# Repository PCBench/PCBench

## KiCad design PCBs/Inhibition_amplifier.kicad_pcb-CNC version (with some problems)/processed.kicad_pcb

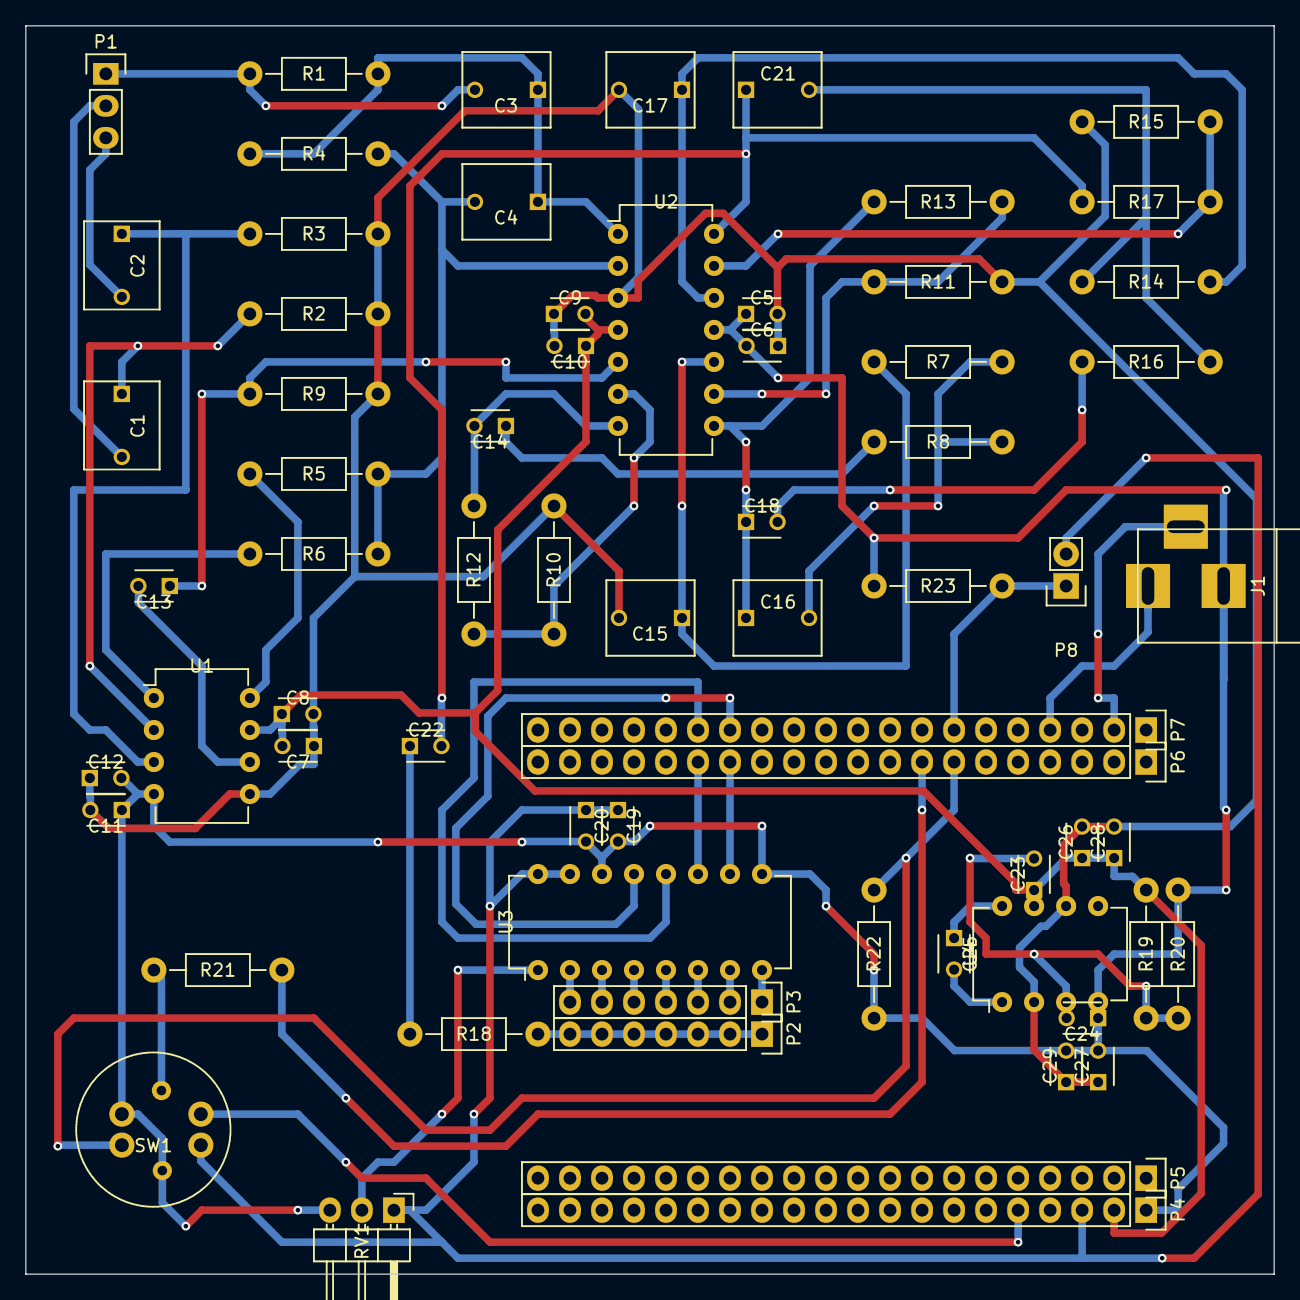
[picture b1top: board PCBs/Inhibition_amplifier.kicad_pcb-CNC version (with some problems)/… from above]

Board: 2 copper layers, 99.1 x 99.1 mm, 67 parts (0 on the bottom side), 51 nets.

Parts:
C1, C2: 0.01μ; C_Rect_L7_W6_P5
C3, C4: 1n; C_Rect_L7_W6_P5
C5, C7, C9, C11, C19: 0.01μ; C_Disc_D3_P2.5
C6, C8, C10, C12, C20: 0.33μ; C_Disc_D3_P2.5
C13, C14, C18, C22, C28, C29: 10μ; C_Disc_D3_P2.5
C15, C17: 0.47μ; C_Rect_L7_W6_P5
C16, C21: 0.82μ; C_Rect_L7_W6_P5
C23, C24: .01μ; C_Disc_D3_P2.5
C25: 1n; C_Disc_D3_P2.5
C26, C27: 1μ; C_Disc_D3_P2.5
J1: JACK_2P; BARREL_JACK
P1: CONN_01X03; Pin_Header_Straight_1x03
P2, P3: CONN_01X07; Pin_Header_Straight_1x07
P4, P5, P6, P7: CONN_01X20; Pin_Header_Straight_1x20
P8: CONN_01X02; Pin_Header_Straight_1x02
R1, R4: 100K; Resistor_Horizontal_RM10mm
R2, R3: 15M; Resistor_Horizontal_RM10mm
R5, R6: 100; Resistor_Horizontal_RM10mm
R7, R8, R9, R10, R11, R14, R15, R16, R19, R22, R23: 10K; Resistor_Horizontal_RM10mm
R12, R13, R17: 470K; Resistor_Horizontal_RM10mm
R18: 220; Resistor_Horizontal_RM10mm
R20: 15K; Resistor_Horizontal_RM10mm
R21: 1K; Resistor_Horizontal_RM10mm
RV1: POT; Pin_Header_Angled_1x03
SW1: Switch_DPST; Switch_LED
U1: AD620; DIP-8_W7.62mm
U2: LM324; DIP-14_W7.62mm
U3: MCP3008; DIP-16_W7.62mm
U4: CA3140; DIP-8_W7.62mm

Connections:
GND: C5.2, C6.1, C7.1, C8.2, C9.1, C10.2, C11.2, C12.1, C15.2, C17.2, C26.2, C27.1, C28.2, C29.1, R2.2, R3.2, R9.2, R10.2, R11.2, R15.2, U1.5, U2.3, U4.2, U4.6
unnamed: C1.1, R2.1, U1.2
unnamed: C1.2, P1.2
unnamed: C2.1, R3.1, U1.3
unnamed: C2.2, P1.3
unnamed: C3.1, C4.1, R1.1, R4.1, U2.1
unnamed: C3.2, P1.1, R1.2
unnamed: C4.2, R4.2, R5.2, R6.1, U2.2
unnamed: C13.1, R9.1, U2.5
unnamed: C13.2, U1.6
unnamed: C14.1, R8.2
unnamed: C14.2, R12.1, U2.7
unnamed: C15.1, R7.1, U2.10
unnamed: C16.1, C18.1, R13.1, U2.8
unnamed: C16.2, R7.2, R8.1
unnamed: C17.1, R14.2, U2.12
unnamed: C18.2, R16.2
unnamed: C19.1, C20.1, P4.3, P8.2, RV1.1, SW1.4, U3.15, U3.16
unnamed: C21.1, C22.2, R17.1, U2.14
unnamed: C21.2, R14.1, R16.1
unnamed: C22.1, R18.1
unnamed: C23.2, C24.2, R19.2, R20.1, U4.3
unnamed: C25.1, U4.8
unnamed: C25.2, U4.1
unnamed: J1.1, P7.4
unnamed: J1.3, P7.2
unnamed: P2.1, P2.2, P2.3, P2.4, P2.5, P2.6, P2.7, R18.2
unnamed: P3.1, U3.8
unnamed: P3.2, U3.7
unnamed: P3.3, U3.6
unnamed: P3.4, U3.5
unnamed: P3.5, U3.4
unnamed: P3.6, U3.3
unnamed: P3.7, U3.2
unnamed: P4.5, SW1.2
unnamed: P6.7, R22.1, SW1.3
unnamed: P6.8, R21.2
unnamed: P6.14, U3.10
unnamed: P6.15, U3.11
unnamed: P7.7, P8.1, R23.1
unnamed: P7.14, U3.13
unnamed: P7.15, U3.12
unnamed: R5.1, U1.8
unnamed: R6.2, U1.1
unnamed: R10.1, R12.2, U2.6
unnamed: R11.1, R13.2, U2.9
unnamed: R15.1, R17.2, U2.13
unnamed: R21.1, SW1.5
unnamed: RV1.2, U3.1
VCC: C7.2, C8.1, C9.2, C10.1, C23.1, C26.1, C28.1, P4.2, R19.1, U1.7, U2.4, U4.7
VEE: C5.1, C6.2, C11.1, C12.2, C19.2, C20.2, C24.1, C27.2, C29.2, J1.2, P4.1, R20.2, R22.2, R23.2, RV1.3, SW1.1, SW1.6, U1.4, U2.11, U3.9, U3.14, U4.4

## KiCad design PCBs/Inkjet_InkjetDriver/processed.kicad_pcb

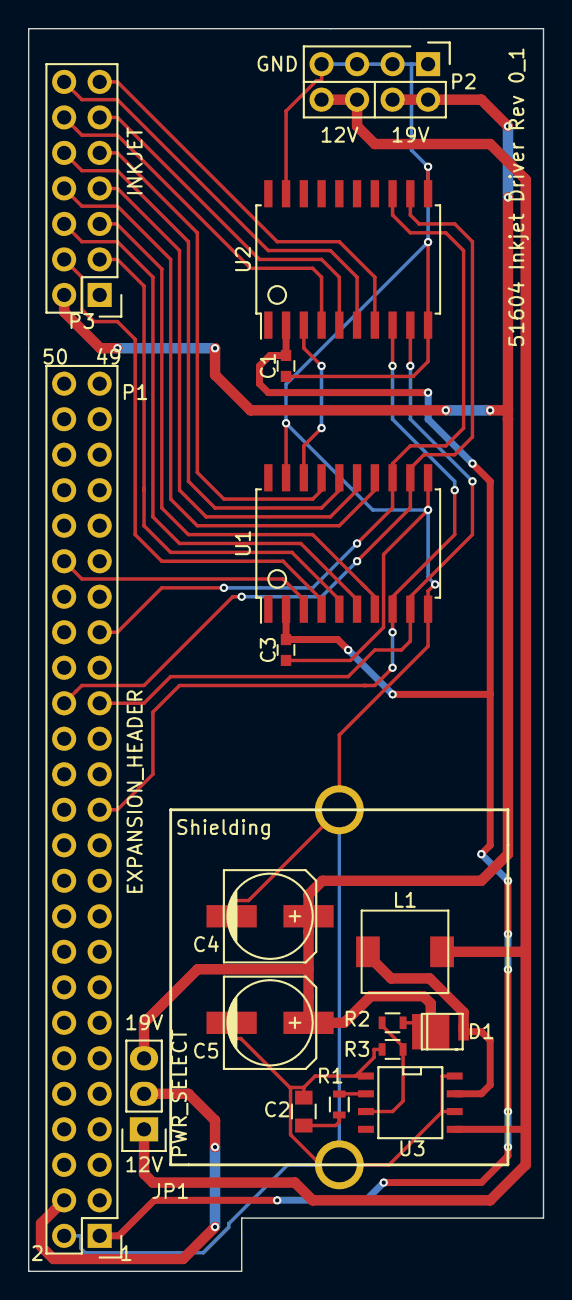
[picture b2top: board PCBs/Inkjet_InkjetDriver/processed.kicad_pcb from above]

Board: 2 copper layers, 36.8 x 88.9 mm, 19 parts (0 on the bottom side), 27 nets.

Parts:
C1, C3: 0.1uF; C_0603
C2: 1uF; C_0805
C4, C5: 100uF; c_elec_6.3x7.7
D1: SS3P4; DO-220_Diode
JP1: PWR_SELECT; Socket_Strip_Straight_1x03
L1: 220uH; CLF6045_Inductor
P1: EXPANSION_HEADER; Pin_Header_Straight_2x25
P2: PWR; Pin_Header_Straight_2x04_Silk_Change
P3: INKJET; Pin_Header_Straight_2x07
R1: 1k; R_0603
R2: 18.7k; R_0603
R3: 1.27k; R_0603
SM1: Shielding; SolderWirePad_single_2-5mmDrill
SM2: Shield; SolderWirePad_single_2-5mmDrill
U1, U2: 6B595; SOIC-20_7.5x12.8mm_Pitch1.27mm
U3: LT1072; SOIC-8-N

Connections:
19V: C4.1, C5.1, D1.1, JP1.3, P2.2, P2.4, P3.2, R2.1
+5V: C1.1, C3.1, P1.1, U1.2, U2.2
+12V: JP1.1, L1.1, P2.6, P2.8, U3.5
GND: C1.2, C2.2, C3.2, C4.2, C5.2, P1.2, P2.1, P2.3, P2.5, P2.7, R3.2, SM1.1, SM2.1, U1.10, U1.11, U1.19, U2.10, U2.11, U2.19, U3.1, U3.6, U3.8
unnamed: C2.1, R1.2
unnamed: D1.2, L1.2, U3.7
unnamed: JP1.2, P1.4
unnamed: P1.25, U1.8, U2.8
unnamed: P1.31, U1.9, U2.9
unnamed: P1.32, U1.12, U2.12
unnamed: P1.35, U1.13, U2.13
unnamed: P1.40, U1.3
unnamed: P3.3, U1.5
unnamed: P3.4, U1.4
unnamed: P3.5, U1.7
unnamed: P3.6, U1.6
unnamed: P3.7, U1.15
unnamed: P3.8, U1.14
unnamed: P3.9, U1.17
unnamed: P3.10, U1.16
unnamed: P3.11, U2.5
unnamed: P3.12, U2.4
unnamed: P3.13, U2.7
unnamed: P3.14, U2.6
unnamed: R1.1, U3.2
unnamed: R2.2, R3.1, U3.3
unnamed: U1.18, U2.3

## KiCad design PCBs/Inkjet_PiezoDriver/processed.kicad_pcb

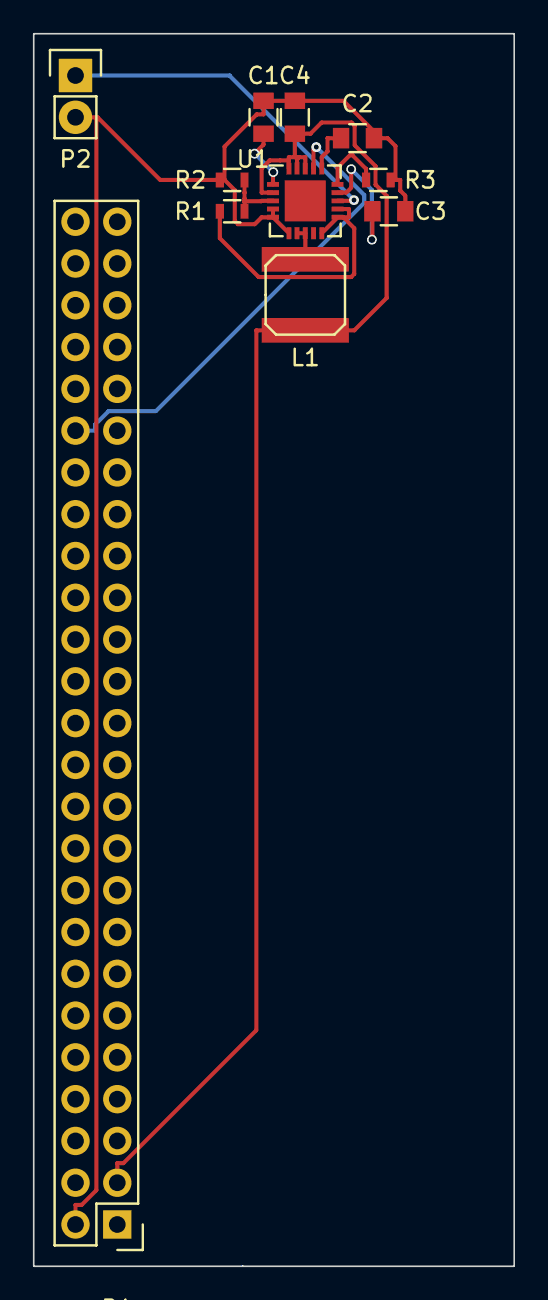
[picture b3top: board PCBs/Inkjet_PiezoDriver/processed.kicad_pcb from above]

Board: 2 copper layers, 29.2 x 74.9 mm, 11 parts (0 on the bottom side), 11 nets.

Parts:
C1, C2, C3, C4: C; C_0805
L1: INDUCTOR; SELF-WE-TPC_M
P1: CONN_02X25; Pin_Header_Straight_2x25
P2: CONN_01X02; Pin_Header_Straight_1x02
R1, R2, R3: R; R_0603
U1: DRV8662; QFN-20-1EP_4x4mm_Pitch0.5mm

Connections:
GND: C1.2, C2.2, C3.2, C4.2, P1.2, P2.2, R2.2, R3.1, U1.4, U1.5, U1.6
unnamed: C1.1, U1.1
unnamed: C2.1, U1.16
unnamed: C3.1, U1.14
unnamed: L1.2, U1.7, U1.8
unnamed: P1.40, U1.17
unnamed: P2.1, U1.13
unnamed: R1.1, U1.10, U1.11, U1.12
unnamed: R1.2, R2.1, U1.3
unnamed: R3.2, U1.15
VDD: C4.1, L1.1, P1.3, U1.2, U1.18, U1.19, U1.20

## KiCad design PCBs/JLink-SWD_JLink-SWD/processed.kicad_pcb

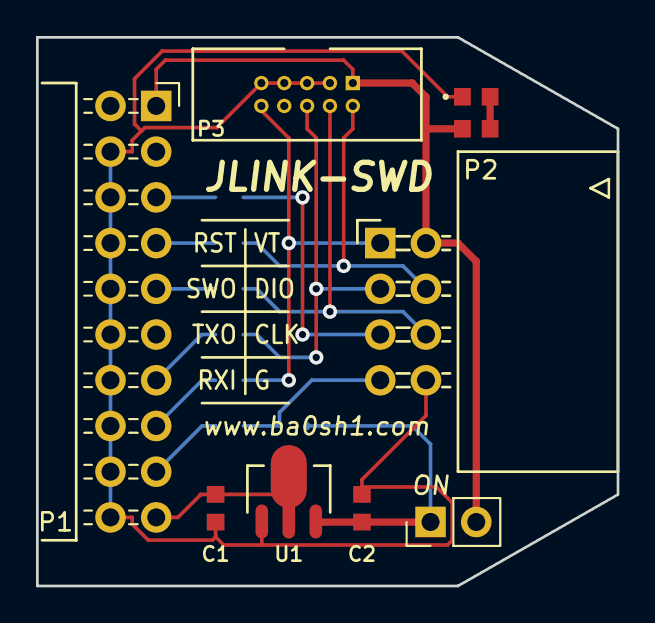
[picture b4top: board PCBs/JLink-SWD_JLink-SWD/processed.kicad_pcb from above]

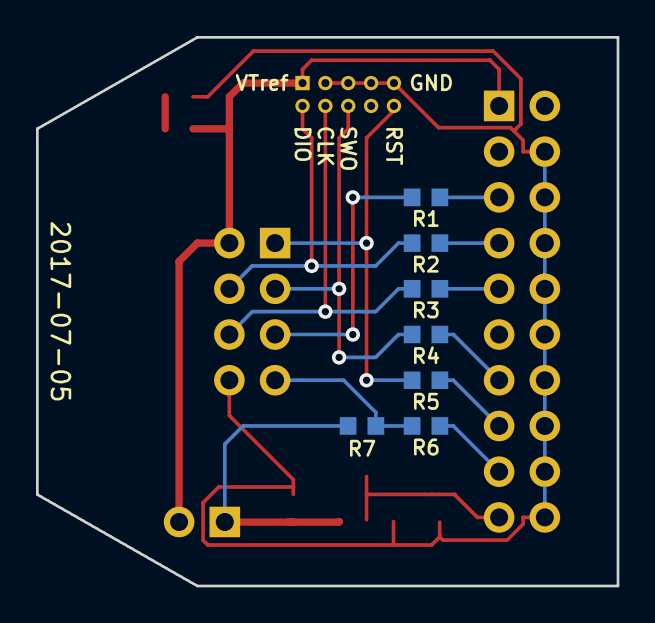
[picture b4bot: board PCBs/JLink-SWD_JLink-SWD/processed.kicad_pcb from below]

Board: 2 copper layers, 32.3 x 30.5 mm, 16 parts (7 on the bottom side), 17 nets.

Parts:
C1: 10u; LC-0603_C
C2: 1u; LC-0603_C
D1: Green; LC-0603_LED
JP1: PWR; Pin_Header_Straight_1x02_Pitch2.54mm
P1: CONN_02X10; Socket_Strip_Angled_2x10_Pitch2.54mm
P2: CONN_02X04; Pin_Header_Angled_2x04_Pitch2.54mm
P3: CONN_02X05; BOX_HEADER_SHROUDED-2x5_50mil
R1, R2, R3, R4, R5, R6: 33R; LC-0603_R
R7, R8: 10K; LC-0603_R
U1: RT9166A-33GXL; LC-SOT-89

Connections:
/3V3: C2.1, JP1.1, R7.1, U1.3
/5VOUT: C1.1, P1.19, U1.2
/RX: P1.17, R6.1
/SWCLK: P1.9, R3.1
/SWDIO: P1.7, R2.1
/SWO: P1.13, R4.1
/TX: P1.5, R1.1
/VTref: JP1.2, P1.1, P2.2, P3.1, R8.1
/nSRST: P1.15, R5.1
GND: C1.2, C2.2, D1.1, P1.4, P1.6, P1.8, P1.10, P1.12, P1.14, P1.16, P1.18, P1.20, P2.8, P3.3, P3.5, P3.7, P3.9, U1.1
unnamed: D1.2, R8.2
unnamed: P2.1, P3.10, R5.2
unnamed: P2.3, P3.6, R4.2
unnamed: P2.4, P3.2, R2.2
unnamed: P2.5, R1.2
unnamed: P2.6, P3.4, R3.2
unnamed: P2.7, R6.2, R7.2
